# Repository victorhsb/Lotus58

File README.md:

# Lotus 58

Starting with simple tweaks to the Lily58 Glow before ordering a set of PCB's it quickly spiraled out of control, and I ended up with what wasn't quite a Lily58 anymore, and although very similar in layout, it is no longer compatible with plate and case design. 

Because of this, it was renamed Lotus58, referencing another flower much like the lily in the name Lily58.

# Lotus 58 Glow

(photo from reddit by u/bduzik)

- Layout very similar to the original Lily58 family
- Per key RGB and RGB underglow
- Kaihl Hot-swap sockets for MX compatible switches
- Can be used as a standalone Gamepad for either hand
- Optional 0.91" OLED Screens and rotary encoders (one each per side)
- All components through-hole and easily soldered for beginners (SMD option for diodes)
- Designed with a sandwich-style plate/case as part of the design

# Layout variations

- Optional plate layout with OLED screen (Encoder can be placed on upper thumb key position)
- Optional plate layout with rotary encoder (Removes OLED screen for that side)  
- Optional plate layout with no hole for OLED or upper encoder (Encoder can be placed on upper thumb key position)

# Parts needed

| Name of part | Qty. | Optional | Remarks | Aliexpress |
| ------------ | ---- | -------- | ------- | --------------- |
| PCB          | 2    | X        | 1,6mm thick | X           |
| Top plate         | 2 | X        | Optional layouts for OLED or encoder in top position. | X |
| Bottom plate         | 2 | X        | X | X |
| Kailh hotswap socket | 56-58 | X | Qty. depends on layout. | [link](https://www.aliexpress.com/item/-/4001051840976.html?spm=a2g0s.8937460.0.0.6f132e0eKYB5RQ&_ga=2.174414626.1036705865.1612730332-979734211.1611132916&_gac=1.119713146.1611132916.CjwKCAiAxp-ABhALEiwAXm6IyZF-HtTdP3MQioG5GOxLvsaJfBbhqTGIQbmV0LXKDx2MZSDJJJTbaBoCPkoQAvD_BwE) |
| Diodes 1N4841 (TH) or 1N4148W (SMD) | 56-58 | X | Qty. depends on layout. TH recommended for beginners. | [link(TH)](https://www.aliexpress.com/item/HOT-SELL-100-PCS-1N4148-DO-35-IN4148-Silicon-Switching-Diode-FREE-SHIPPMENT/32660088529.html?spm=a2g0s.8937460.0.0.c1b82e0edjrOT3&_ga=2.216963734.1036705865.1612730332-979734211.1611132916&_gac=1.53192282.1611132916.CjwKCAiAxp-ABhALEiwAXm6IyZF-HtTdP3MQioG5GOxLvsaJfBbhqTGIQbmV0LXKDx2MZSDJJJTbaBoCPkoQAvD_BwE) or [link(SMD)](https://www.aliexpress.ru/item/-/1005002059571417.html?spm=a2g0s.8937460.0.0.c1b82e0edjrOT3&_ga=2.216963734.1036705865.1612730332-979734211.1611132916&_gac=1.53192282.1611132916.CjwKCAiAxp-ABhALEiwAXm6IyZF-HtTdP3MQioG5GOxLvsaJfBbhqTGIQbmV0LXKDx2MZSDJJJTbaBoCPkoQAvD_BwE) |
| Capacitors 100 nF | 0-4 | ✔ | Qty. depends on layout. 2 needed for each encoder installed. | [link](https://www.aliexpress.com/item/-/32971478818.html?spm=a2g0s.8937460.0.0.6f132e0eKYB5RQ&_ga=2.149198518.1036705865.1612730332-979734211.1611132916&_gac=1.48473428.1611132916.CjwKCAiAxp-ABhALEiwAXm6IyZF-HtTdP3MQioG5GOxLvsaJfBbhqTGIQbmV0LXKDx2MZSDJJJTbaBoCPkoQAvD_BwE) |
| Resistor 4.7 kOhm | 2 | X | Meant to be mounted only on one side | [link](https://www.aliexpress.com/item/-/32847047012.html?spm=a2g0s.8937460.0.0.c1b82e0edjrOT3&_ga=2.241041155.1036705865.1612730332-979734211.1611132916&_gac=1.219449963.1611132916.CjwKCAiAxp-ABhALEiwAXm6IyZF-HtTdP3MQioG5GOxLvsaJfBbhqTGIQbmV0LXKDx2MZSDJJJTbaBoCPkoQAvD_BwE) |
| 0.91" OLED Display | 0-2 | ✔ | Qty. depends on layout. | [link](https://www.aliexpress.com/item/-/4001028384269.html?spm=a2g0s.8937460.0.0.c1b82e0edjrOT3&_ga=2.241041155.1036705865.1612730332-979734211.1611132916&_gac=1.219449963.1611132916.CjwKCAiAxp-ABhALEiwAXm6IyZF-HtTdP3MQioG5GOxLvsaJfBbhqTGIQbmV0LXKDx2MZSDJJJTbaBoCPkoQAvD_BwE) |
| TRRS jack PJ-320A | 2 | X | X | [link](https://www.aliexpress.com/item/-/4000114275750.html?spm=a2g0s.8937460.0.0.c1b82e0edjrOT3&_ga=2.148895671.1036705865.1612730332-979734211.1611132916&_gac=1.262958974.1611132916.CjwKCAiAxp-ABhALEiwAXm6IyZF-HtTdP3MQioG5GOxLvsaJfBbhqTGIQbmV0LXKDx2MZSDJJJTbaBoCPkoQAvD_BwE) |
| M2 * 10 mm standoff | 10 | X | Rounded, max 3.7 mm in diameter | [link](https://www.aliexpress.com/item/-/32863484622.html?spm=a2g0s.8937460.0.0.c1b82e0edjrOT3&_ga=2.215809815.1036705865.1612730332-979734211.1611132916&_gac=1.26395343.1611132916.CjwKCAiAxp-ABhALEiwAXm6IyZF-HtTdP3MQioG5GOxLvsaJfBbhqTGIQbmV0LXKDx2MZSDJJJTbaBoCPkoQAvD_BwE) |
| M2 * 4 mm screw | 20 | X | 4-8 mm length fits, low profile hex head recommended | [link](https://www.aliexpress.com/item/-/32966917947.html?spm=a2g0s.8937460.0.0.c1b82e0edjrOT3&_ga=2.246923140.1036705865.1612730332-979734211.1611132916&_gac=1.263439230.1611132916.CjwKCAiAxp-ABhALEiwAXm6IyZF-HtTdP3MQioG5GOxLvsaJfBbhqTGIQbmV0LXKDx2MZSDJJJTbaBoCPkoQAvD_BwE) |
| TRRS cable | 1 | X | Needs to be 4 poles, more common 3 poles cable creates a shortcircuit | [link](https://www.aliexpress.com/item/32905903526.html?spm=a2g0o.productlist.0.0.1ea55b40PsHOY6&algo_pvid=74ac6da4-21fa-4152-a7a7-805ba558a2d8&algo_expid=74ac6da4-21fa-4152-a7a7-805ba558a2d8-1&btsid=2100bb4c16148500192992030ee115&ws_ab_test=searchweb0_0,searchweb201602_,searchweb201603_) |
| Silicon pads | 10 | X | X | [link](https://www.aliexpress.com/item/-/32912066603.html?spm=a2g0s.8937460.0.0.6f132e0eKYB5RQ&_ga=2.145547188.1036705865.1612730332-979734211.1611132916&_gac=1.57255896.1611132916.CjwKCAiAxp-ABhALEiwAXm6IyZF-HtTdP3MQioG5GOxLvsaJfBbhqTGIQbmV0LXKDx2MZSDJJJTbaBoCPkoQAvD_BwE) |
| Pro Micro | 2 | X | Can be built with various ProMicro clones as well as Elite C (Or nice!nano for a wireless keyboard) | [link](https://www.aliexpress.com/item/-/32849563958.html?spm=a2g0s.8937460.0.0.c1b82e0edjrOT3&_ga=2.175422242.1036705865.1612730332-979734211.1611132916&_gac=1.225165928.1611132916.CjwKCAiAxp-ABhALEiwAXm6IyZF-HtTdP3MQioG5GOxLvsaJfBbhqTGIQbmV0LXKDx2MZSDJJJTbaBoCPkoQAvD_BwE) |
| Rotary Encoder | 0-2 | ✔ | Qty. depends on layout. | [link](https://www.aliexpress.com/item/10000056483250.html?spm=a2g0o.productlist.0.0.64951c5fKcPiug&algo_pvid=b530d9b1-fbd2-4598-bf53-bece1343826f&algo_expid=b530d9b1-fbd2-4598-bf53-bece1343826f-2&btsid=2100bdd016135510210168102eefcc&ws_ab_test=searchweb0_0,searchweb201602_,searchweb201603_) |
| Rotary Encoder Knob | 0-2 | ✔ | One needed for each encoder. Clearance for max 24 mm diameter, pick halfshaft or spline according to encoder choice.  | [link](https://www.aliexpress.com/item/10000056483250.html?spm=a2g0o.productlist.0.0.64951c5fKcPiug&algo_pvid=b530d9b1-fbd2-4598-bf53-bece1343826f&algo_expid=b530d9b1-fbd2-4598-bf53-bece1343826f-2&btsid=2100bdd016135510210168102eefcc&ws_ab_test=searchweb0_0,searchweb201602_,searchweb201603_) |
| SK6812 mini (3535) | 56-70 | ✔ | Qty. depends on layout. Optional 12 pcs required for underglow. | [link](https://www.aliexpress.com/item/-/4001361956752.html?spm=a2g0s.8937460.0.0.6f132e0eCg84IE&_ga=2.137862832.1036705865.1612730332-979734211.1611132916&_gac=1.14797764.1611132916.CjwKCAiAxp-ABhALEiwAXm6IyZF-HtTdP3MQioG5GOxLvsaJfBbhqTGIQbmV0LXKDx2MZSDJJJTbaBoCPkoQAvD_BwE) |

# Things to note when ordering PCB's

**If you are not aiming at modifying things, don't look for the gerber files in the folders, pretty please! And don't open yet another issue about it! The gerber files are where they belong, zipped up in releases.**

Most PCB manufacturers have a MOQ of 5 PCB's, meaning you end up with 2½ keyboards when finished. To make it possible to build Lotus58 at a reasonable cost, the plate designs use breakaway parts and can easily double as a backplate. For instance, 5 PCB's + 5 OLED plates + 5 Encoder plates give you a couple of options without being wasteful.  

The recommended PCB thickness is 1.6 mm, as the thickness of the SK6812mini RGB LED's are in fact 1.6 mm, making them sit flush 'inside' the PCB and easier to solder. Similarly, for the top plate, a thickness of 1.6 mm is recommended to allow the keyswitches to grip the plate and lock in place securely.

If ordering from [JLPCB](https://www.jlpcb.com) the plate Gerber files include a reference putting the added serial etc on a breakaway part for a clean look with minimal cost, if using another manufacturer it's possible they have additional fee's for removing the extra text, or you should consider plotting the Gerber files yourself with the correct reference for your manufacturer.

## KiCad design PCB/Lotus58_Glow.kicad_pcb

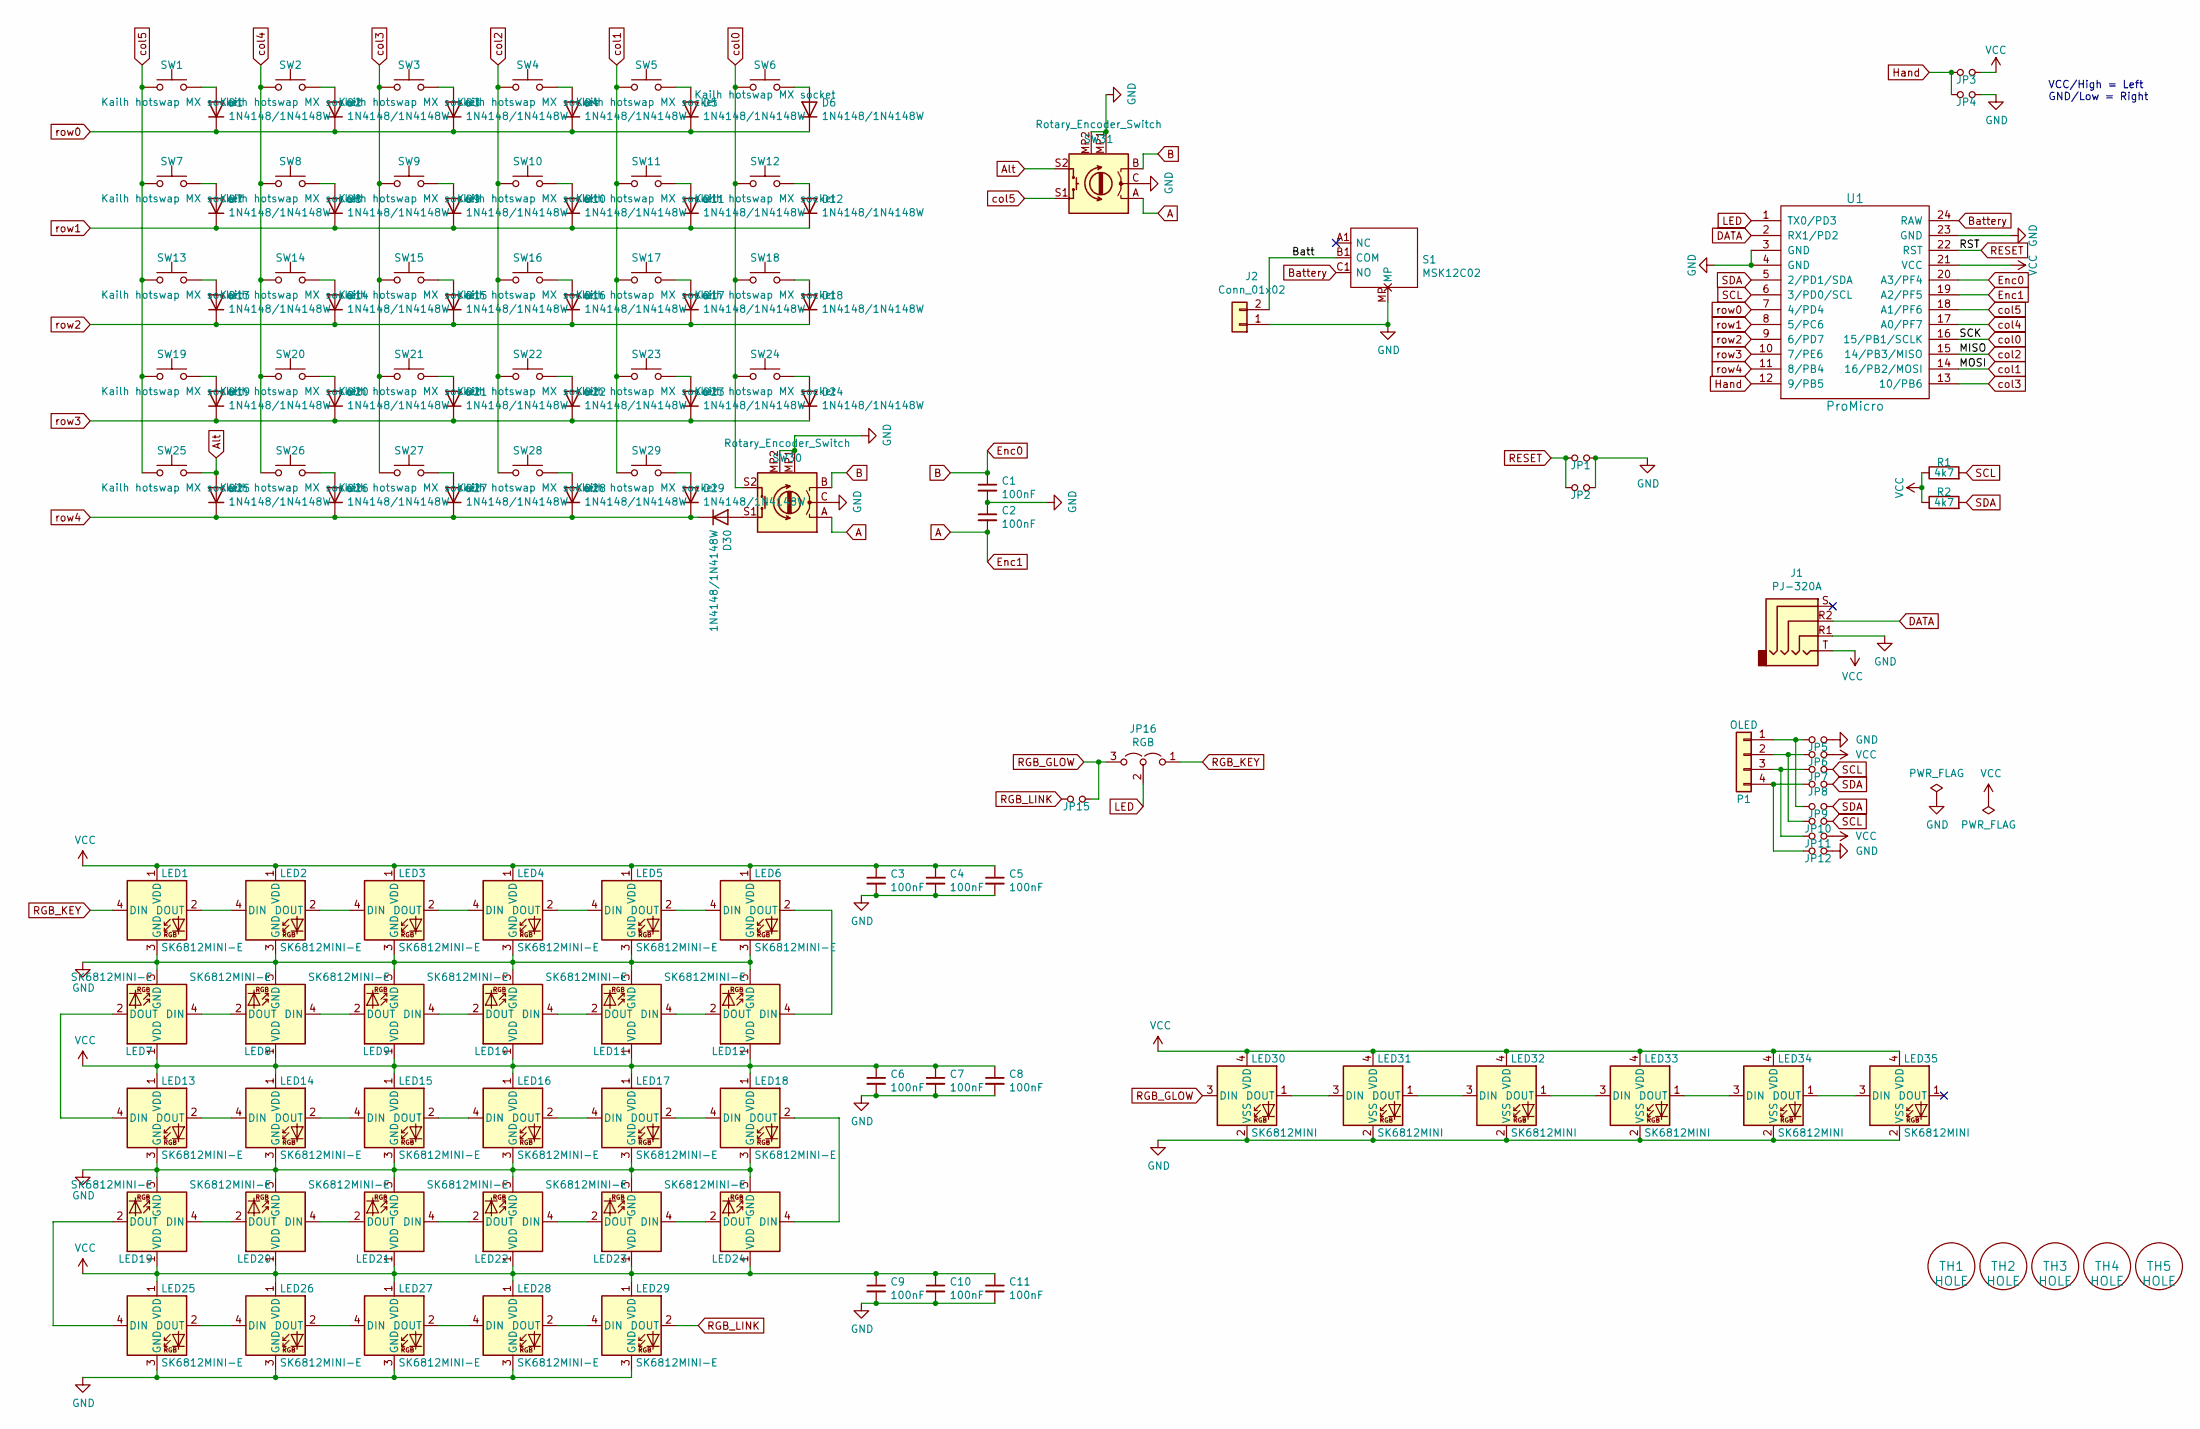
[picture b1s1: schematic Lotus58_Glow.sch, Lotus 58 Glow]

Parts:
C1, C2, C3, C4, C5, C6, C7, C8, C9, C10, C11: 100nF; RESISTOR_Reversible
D1, D2, D3, D4, D5, D6, D7, D8, D9, D10, D11, D12, D13, D14, D15, D16, D17, D18, D19, D20, D21, D22, D23, D24, D25, D26, D27, D28, D29, D30: 1N4148/1N4148W; Diode_DO35_SOD123
J1: PJ-320A; MJ-4PP-9_alim
J2: Conn_01x02; PinHeader_1x02_P2.54mm_Vertical
JP1, JP2: RESET; Jumper_Mini
JP3: LEFT; Jumper_Mini
JP4: RIGHT; Jumper_Mini
JP5, JP6, JP7, JP8, JP9, JP10, JP11, JP12: Jumper_NO_Small; Jumper_Mini
JP15: FULL; Jumper_Mini
JP16: RGB; SolderJumper-3_P1.3mm_Open_Pad1.0x1.5mm
LED1, LED2, LED3, LED4, LED5, LED6, LED7, LED8, LED9, LED10, LED11, LED12, LED13, LED14, LED15, LED16, LED17, LED18, LED19, LED20, LED21, LED22, LED23, LED24, LED25, LED26, LED27, LED28, LED29: SK6812MINI-E; MX_SK6812MINI-E_REVERSIBLE
LED30, LED31, LED32, LED33, LED34, LED35: SK6812MINI; LED_SK6812MINI_PLCC4_3.5x3.5mm_P1.75mm
P1: OLED; SSD1306-0.91-OLED-4pin-128x32
R1, R2: 4k7; R_Axial_DIN0207_L6.3mm_D2.5mm_P7.62mm_Horizontal
S1: MSK12C02; Manufacturer_Part_Number MSK12C02
SW1, SW2, SW3, SW4, SW5, SW6, SW7, SW8, SW9, SW10, SW11, SW12, SW13, SW14, SW15, SW16, SW17, SW18, SW19, SW20, SW21, SW22, SW23, SW24, SW25, SW26, SW27, SW28, SW29: Kailh hotswap MX socket; Kailh_socket_MX_reversible_RGB
SW30: Rotary_Encoder_Switch; RotaryEncoder_Alps_EC11E-Switch_Vertical_H20_special
SW31: Rotary_Encoder_Switch; RotaryEncoder_Alps_EC11E-Switch_Special
TH1, TH2, TH3, TH4, TH5: HOLE; MountingHole_3.7mm
U1: ProMicro; ProMicro_Reversible

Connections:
/Batt: J2.2, S1.B1 (COM)
A: C2.2, SW30.A, SW31.A, U1.19 (A2/PF5)
Alt: D25.2 (A), SW25.2, SW31.S2
B: C1.1, SW30.B, SW31.B, U1.20 (A3/PF4)
Battery: S1.C1 (NO), U1.24 (RAW)
DATA: J1.R2, U1.2 (RX1/PD2)
GND: C1.2, C2.1, C3.2, C4.2, C5.2, C6.2, C7.2, C8.2, C9.2, C10.2, C11.2, J1.R1, J2.1, JP1.2, JP2.2, JP4.2, JP5.2, JP12.2, LED1.3 (GND), LED2.3 (GND), LED3.3 (GND), LED4.3 (GND), LED5.3 (GND), LED6.3 (GND), LED7.3 (GND), LED8.3 (GND), LED9.3 (GND), LED10.3 (GND), LED11.3 (GND), LED12.3 (GND), LED13.3 (GND), LED14.3 (GND), LED15.3 (GND), LED16.3 (GND), LED17.3 (GND), LED18.3 (GND), LED19.3 (GND), LED20.3 (GND), LED21.3 (GND), LED22.3 (GND), LED23.3 (GND), LED24.3 (GND), LED25.3 (GND), LED26.3 (GND), LED27.3 (GND), LED28.3 (GND), LED29.3 (GND), LED30.2 (VSS), LED31.2 (VSS), LED32.2 (VSS), LED33.2 (VSS), LED34.2 (VSS), LED35.2 (VSS), S1.MP, SW30.C, SW30.MP1 (GND), SW30.MP2 (GND), SW31.C, SW31.MP1 (GND), SW31.MP2 (GND), U1.3 (GND), U1.4 (GND), U1.23 (GND)
Hand: JP3.1, JP4.1, U1.12 (9/PB5)
LED: JP16.2 (C), U1.1 (TX0/PD3)
unnamed: D1.2 (A), SW1.2
unnamed: D2.2 (A), SW2.2
unnamed: D3.2 (A), SW3.2
unnamed: D4.2 (A), SW4.2
unnamed: D5.2 (A), SW5.2
unnamed: D6.2 (A), SW6.2
unnamed: D7.2 (A), SW7.2
unnamed: D8.2 (A), SW8.2
unnamed: D9.2 (A), SW9.2
unnamed: D10.2 (A), SW10.2
unnamed: D11.2 (A), SW11.2
unnamed: D12.2 (A), SW12.2
unnamed: D13.2 (A), SW13.2
unnamed: D14.2 (A), SW14.2
unnamed: D15.2 (A), SW15.2
unnamed: D16.2 (A), SW16.2
unnamed: D17.2 (A), SW17.2
unnamed: D18.2 (A), SW18.2
unnamed: D19.2 (A), SW19.2
unnamed: D20.2 (A), SW20.2
unnamed: D21.2 (A), SW21.2
unnamed: D22.2 (A), SW22.2
unnamed: D23.2 (A), SW23.2
unnamed: D24.2 (A), SW24.2
unnamed: D26.2 (A), SW26.2
unnamed: D27.2 (A), SW27.2
unnamed: D28.2 (A), SW28.2
unnamed: D29.2 (A), SW29.2
unnamed: D30.2 (A), SW30.S1
unnamed: JP5.1, JP9.1, P1.1
unnamed: JP6.1, JP10.1, P1.2
unnamed: JP7.1, JP11.1, P1.3
unnamed: JP8.1, JP12.1, P1.4
unnamed: LED1.2 (DOUT), LED2.4 (DIN)
unnamed: LED2.2 (DOUT), LED3.4 (DIN)
unnamed: LED3.2 (DOUT), LED4.4 (DIN)
unnamed: LED4.2 (DOUT), LED5.4 (DIN)
unnamed: LED5.2 (DOUT), LED6.4 (DIN)
unnamed: LED7.4 (DIN), LED8.2 (DOUT)
unnamed: LED8.4 (DIN), LED9.2 (DOUT)
unnamed: LED9.4 (DIN), LED10.2 (DOUT)
unnamed: LED10.4 (DIN), LED11.2 (DOUT)
unnamed: LED11.4 (DIN), LED12.2 (DOUT)
unnamed: LED6.2 (DOUT), LED12.4 (DIN)
unnamed: LED13.2 (DOUT), LED14.4 (DIN)
unnamed: LED7.2 (DOUT), LED13.4 (DIN)
unnamed: LED14.2 (DOUT), LED15.4 (DIN)
unnamed: LED15.2 (DOUT), LED16.4 (DIN)
unnamed: LED16.2 (DOUT), LED17.4 (DIN)
unnamed: LED17.2 (DOUT), LED18.4 (DIN)
unnamed: LED18.2 (DOUT), LED24.4 (DIN)
unnamed: LED19.2 (DOUT), LED25.4 (DIN)
unnamed: LED19.4 (DIN), LED20.2 (DOUT)
unnamed: LED20.4 (DIN), LED21.2 (DOUT)
unnamed: LED21.4 (DIN), LED22.2 (DOUT)
unnamed: LED22.4 (DIN), LED23.2 (DOUT)
unnamed: LED23.4 (DIN), LED24.2 (DOUT)
unnamed: LED25.2 (DOUT), LED26.4 (DIN)
unnamed: LED26.2 (DOUT), LED27.4 (DIN)
unnamed: LED27.2 (DOUT), LED28.4 (DIN)
unnamed: LED28.2 (DOUT), LED29.4 (DIN)
unnamed: LED30.1 (DOUT), LED31.3 (DIN)
unnamed: LED31.1 (DOUT), LED32.3 (DIN)
unnamed: LED32.1 (DOUT), LED33.3 (DIN)
unnamed: LED33.1 (DOUT), LED34.3 (DIN)
unnamed: LED34.1 (DOUT), LED35.3 (DIN)
RESET: JP1.1, JP2.1, U1.22 (RST)
RGB_GLOW: JP15.2, JP16.3 (B), LED30.3 (DIN)
RGB_KEY: JP16.1 (A), LED1.4 (DIN)
RGB_LINK: JP15.1, LED29.2 (DOUT)
SCL: JP7.2, JP10.2, R1.2, U1.6 (3/PD0/SCL)
SDA: JP8.2, JP9.2, R2.2, U1.5 (2/PD1/SDA)
VCC: C3.1, C4.1, C5.1, C6.1, C7.1, C8.1, C9.1, C10.1, C11.1, J1.T, JP3.2, JP6.2, JP11.2, LED1.1 (VDD), LED2.1 (VDD), LED3.1 (VDD), LED4.1 (VDD), LED5.1 (VDD), LED6.1 (VDD), LED7.1 (VDD), LED8.1 (VDD), LED9.1 (VDD), LED10.1 (VDD), LED11.1 (VDD), LED12.1 (VDD), LED13.1 (VDD), LED14.1 (VDD), LED15.1 (VDD), LED16.1 (VDD), LED17.1 (VDD), LED18.1 (VDD), LED19.1 (VDD), LED20.1 (VDD), LED21.1 (VDD), LED22.1 (VDD), LED23.1 (VDD), LED24.1 (VDD), LED25.1 (VDD), LED26.1 (VDD), LED27.1 (VDD), LED28.1 (VDD), LED29.1 (VDD), LED30.4 (VDD), LED31.4 (VDD), LED32.4 (VDD), LED33.4 (VDD), LED34.4 (VDD), LED35.4 (VDD), R1.1, R2.1, U1.21 (VCC)
col0: SW6.1, SW12.1, SW18.1, SW24.1, SW30.S2, U1.16 (15/PB1/SCLK)
col1: SW5.1, SW11.1, SW17.1, SW23.1, SW29.1, U1.14 (16/PB2/MOSI)
col2: SW4.1, SW10.1, SW16.1, SW22.1, SW28.1, U1.15 (14/PB3/MISO)
col3: SW3.1, SW9.1, SW15.1, SW21.1, SW27.1, U1.13 (10/PB6)
col4: SW2.1, SW8.1, SW14.1, SW20.1, SW26.1, U1.17 (A0/PF7)
col5: SW1.1, SW7.1, SW13.1, SW19.1, SW25.1, SW31.S1, U1.18 (A1/PF6)
row0: D1.1 (K), D2.1 (K), D3.1 (K), D4.1 (K), D5.1 (K), D6.1 (K), U1.7 (4/PD4)
row1: D7.1 (K), D8.1 (K), D9.1 (K), D10.1 (K), D11.1 (K), D12.1 (K), U1.8 (5/PC6)
row2: D13.1 (K), D14.1 (K), D15.1 (K), D16.1 (K), D17.1 (K), D18.1 (K), U1.9 (6/PD7)
row3: D19.1 (K), D20.1 (K), D21.1 (K), D22.1 (K), D23.1 (K), D24.1 (K), U1.10 (7/PE6)
row4: D25.1 (K), D26.1 (K), D27.1 (K), D28.1 (K), D29.1 (K), D30.1 (K), U1.11 (8/PB4)

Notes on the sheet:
VCC/High = Left GND/Low = Right

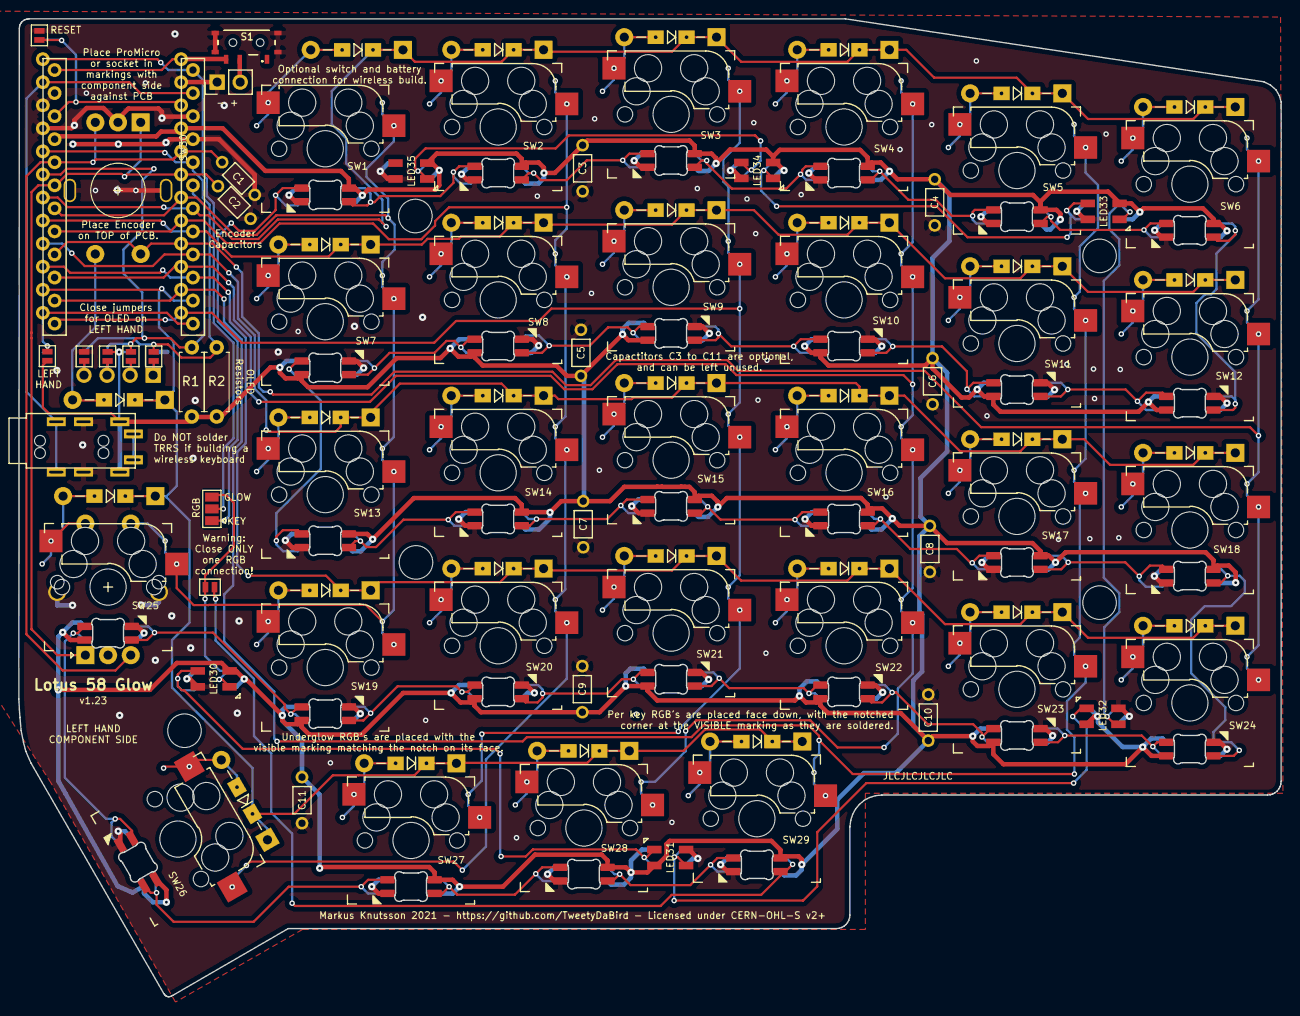
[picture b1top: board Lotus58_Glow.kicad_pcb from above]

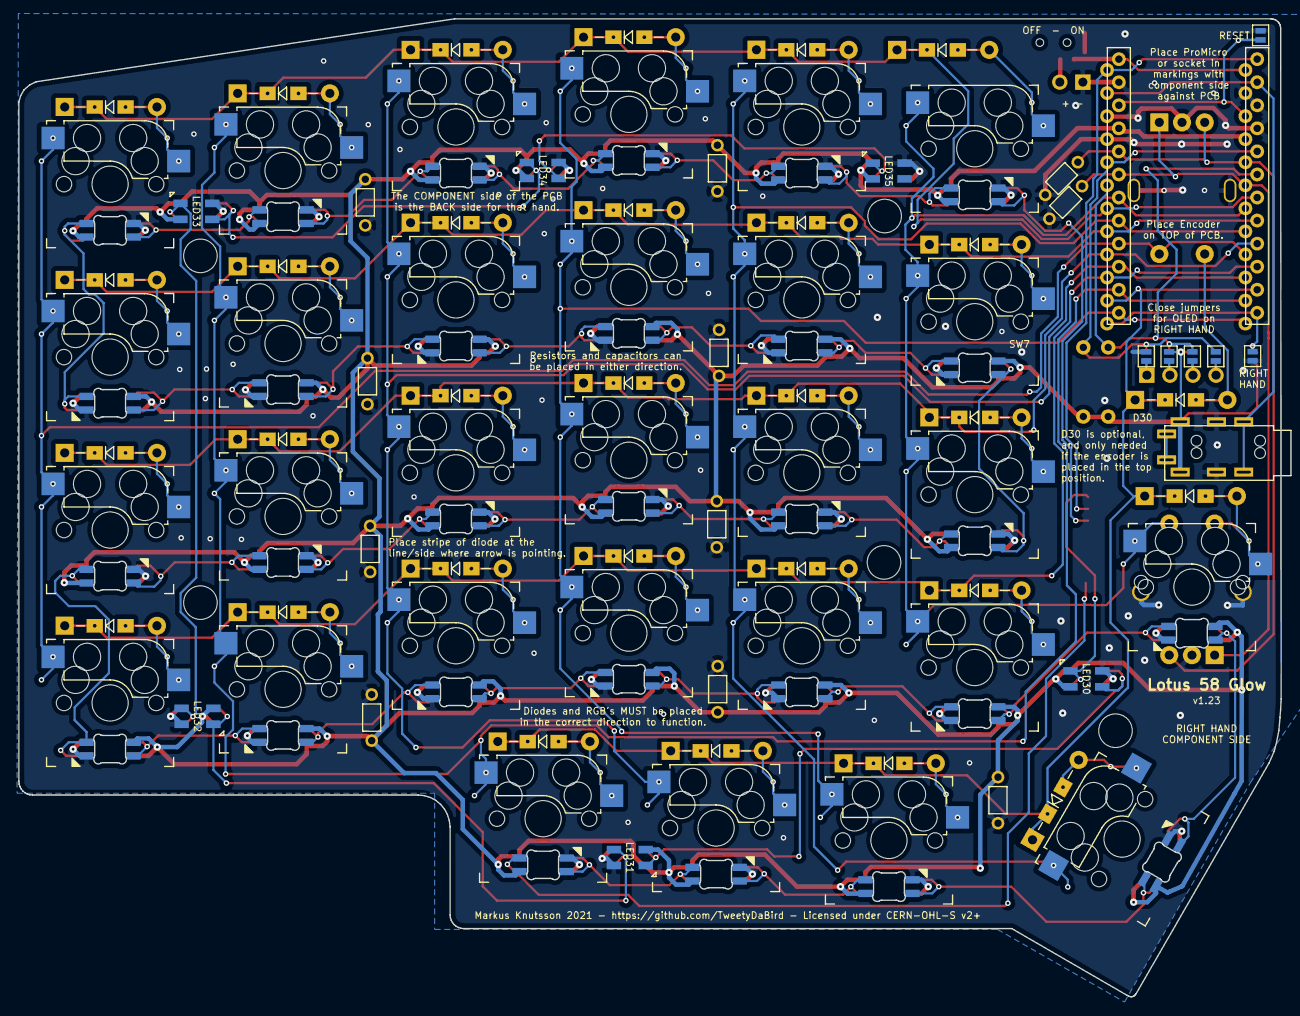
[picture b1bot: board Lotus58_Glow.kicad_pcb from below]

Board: 2 copper layers, 139.1 x 107.7 mm, 133 parts (38 on the bottom side), 93 nets.

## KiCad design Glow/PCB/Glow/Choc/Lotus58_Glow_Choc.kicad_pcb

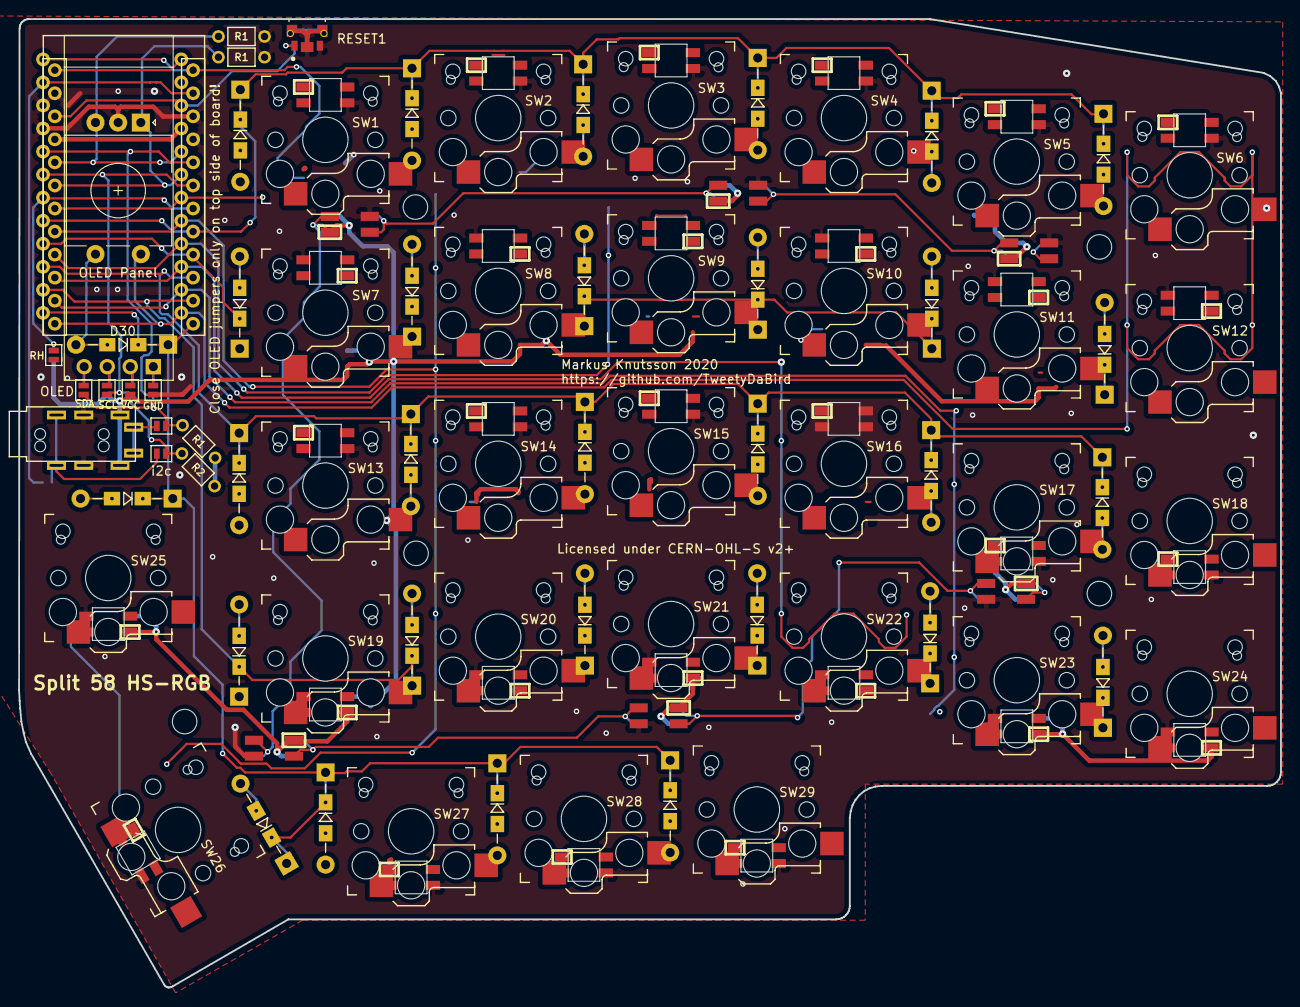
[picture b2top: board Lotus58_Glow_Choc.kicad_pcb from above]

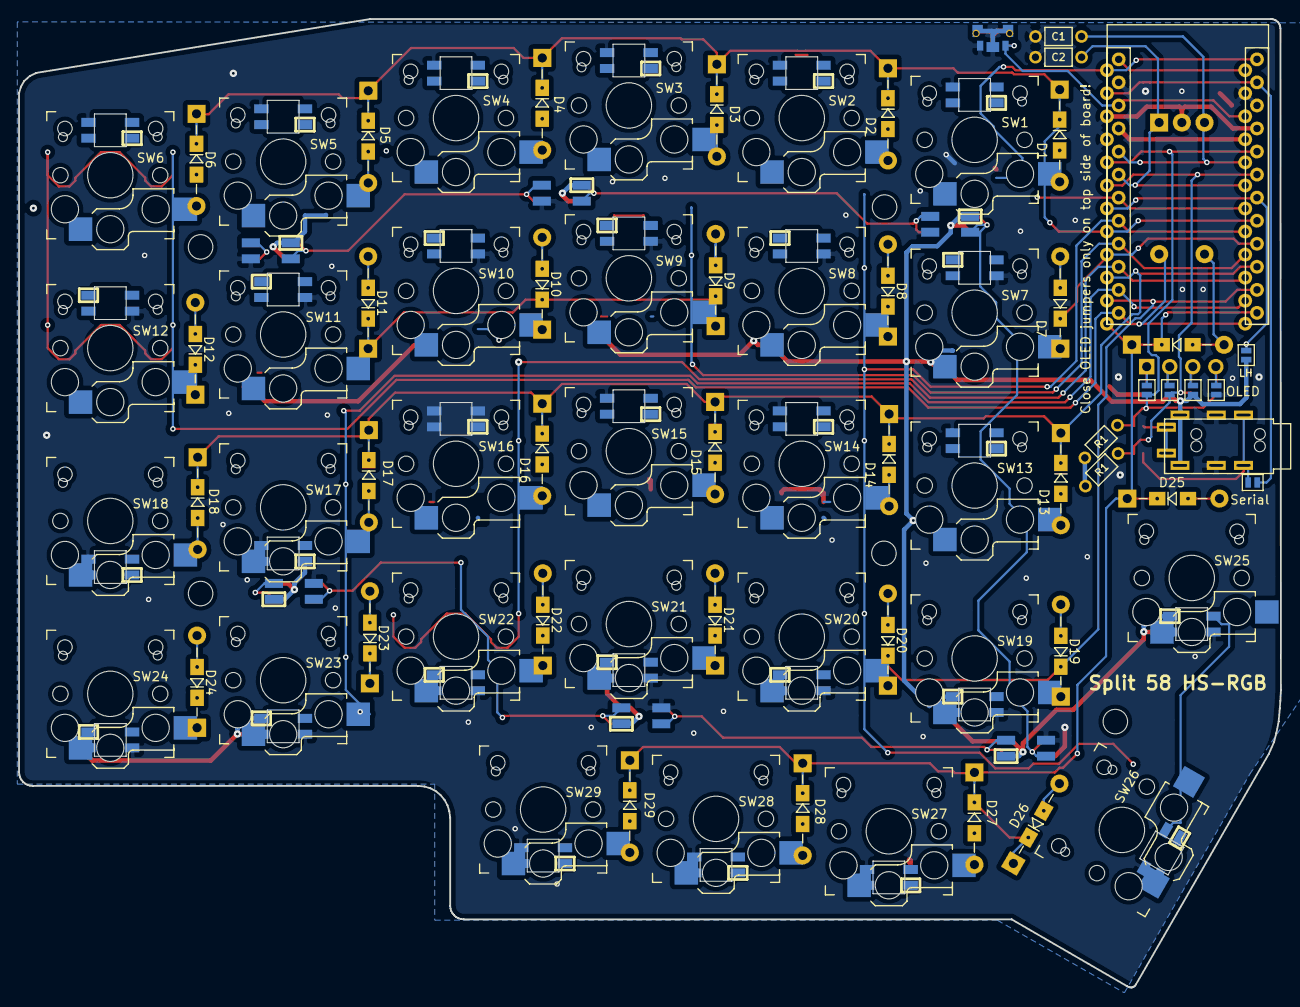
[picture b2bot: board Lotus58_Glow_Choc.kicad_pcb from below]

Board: 2 copper layers, 139.1 x 106.7 mm, 121 parts (37 on the bottom side), 91 nets.

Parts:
C1, C2: C_Small; RESISTOR_Reversible
D1, D2, D3, D4, D5, D6, D7, D8, D9, D10, D11, D12, D13, D14, D15, D16, D17, D18, D19, D20, D21, D22, D23, D24, D25, D26, D27, D28, D29, D30: D; Diode_DO35_SOD123
J1: AudioJack4; MJ-4PP-9_alim
JP1, JP2, JP3, JP4, JP5, JP6, JP7, JP8, JP9, JP10, JP11: Jumper_NO_Small; Jumper_Mini
JP12: LH; Jumper_Mini
JP13: RH; Jumper_Mini
L1, L2, L3, L4, L5, L6, L7, L8, L9, L10, L11, L12, L13, L14, L15, L16, L17, L18, L19, L20, L21, L22, L23, L24, L25, L26, L27, L28, L29: SK6812mini; SK6812MINI_Midmount_Reversible
L30, L31, L32, L33, L34, L35: SK6812mini; SK6812MINI_Reversible
P4: OLED; SSD1306-0.91-OLED-4pin-128x32
R1, R2: R; RESISTOR_Reversible
RESET1: EVP-AKE31A; Panasonic-EVP-AKE31A-MFG_reversible
SW1, SW2, SW3, SW4, SW5, SW6, SW7, SW8, SW9, SW10, SW11, SW12, SW13, SW14, SW15, SW16, SW17, SW18, SW19, SW20, SW21, SW22, SW23, SW24, SW25, SW26, SW27, SW28, SW29: SW_PUSH; Kailh_socket_PG1350_PG1353_reversible
SW30: Rotary_Encoder_Switch; RotaryEncoder_EC11-no-legs
TH3, TH4, TH5, TH6, TH7: HOLE; MountingHole_2.7mm_M2.5
U1: ProMicro; ProMicro_Reversible

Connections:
DATA: JP11.2, U1.2
Enc0: C1.1, SW30.B, U1.20
Enc1: C2.2, SW30.A, U1.19
GND: C1.2, C2.1, J1.R1, JP1.2, JP8.2, JP13.2, L1.2, L2.2, L3.2, L4.2, L5.2, L6.2, L7.2, L8.2, L9.2, L10.2, L11.2, L12.2, L13.2, L14.2, L15.2, L16.2, L17.2, L18.2, L19.2, L20.2, L21.2, L22.2, L23.2, L24.2, L25.2, L26.2, L27.2, L28.2, L29.2, L30.2, L31.2, L32.2, L33.2, L34.2, L35.2, RESET1.1, RESET1.2, RESET1.3, RESET1.A, SW30.C, U1.3, U1.4, U1.23
Hand: JP12.1, JP13.1, U1.7
LED: L1.3, U1.1
unnamed: D1.2, SW1.2
unnamed: D2.2, SW2.2
unnamed: D3.2, SW3.2
unnamed: D4.2, SW4.2
unnamed: D5.2, SW5.2
unnamed: D6.2, SW6.2
unnamed: D7.2, SW7.2
unnamed: D8.2, SW8.2
unnamed: D9.2, SW9.2
unnamed: D10.2, SW10.2
unnamed: D11.2, SW11.2
unnamed: D12.2, SW12.2
unnamed: D13.2, SW13.2
unnamed: D14.2, SW14.2
unnamed: D15.2, SW15.2
unnamed: D16.2, SW16.2
unnamed: D17.2, SW17.2
unnamed: D18.2, SW18.2
unnamed: D19.2, SW19.2
unnamed: D20.2, SW20.2
unnamed: D21.2, SW21.2
unnamed: D22.2, SW22.2
unnamed: D23.2, SW23.2
unnamed: D24.2, SW24.2
unnamed: D25.2, SW25.2
unnamed: D26.2, SW26.2
unnamed: D27.2, SW27.2
unnamed: D28.2, SW28.2
unnamed: D29.2, SW29.2
unnamed: D30.2, SW30.S1
unnamed: J1.R2, JP9.2, JP11.1
unnamed: J1.S, JP10.1
unnamed: JP1.1, JP5.1, P4.1
unnamed: JP2.1, JP6.1, P4.2
unnamed: JP3.1, JP7.1, P4.3
unnamed: JP4.1, JP8.1, P4.4
unnamed: L1.1, L2.3
unnamed: L2.1, L3.3
unnamed: L3.1, L4.3
unnamed: L4.1, L5.3
unnamed: L5.1, L6.3
unnamed: L7.3, L8.1
unnamed: L8.3, L9.1
unnamed: L9.3, L10.1
unnamed: L10.3, L11.1
unnamed: L11.3, L12.1
unnamed: L6.1, L12.3
unnamed: L13.1, L14.3
unnamed: L7.1, L13.3
unnamed: L14.1, L15.3
unnamed: L15.1, L16.3
unnamed: L16.1, L17.3
unnamed: L17.1, L18.3
unnamed: L18.1, L24.3
unnamed: L19.1, L25.3
unnamed: L19.3, L20.1
unnamed: L20.3, L21.1
unnamed: L21.3, L22.1
unnamed: L22.3, L23.1
unnamed: L23.3, L24.1
unnamed: L25.1, L26.3
unnamed: L26.1, L27.3
unnamed: L27.1, L28.3
unnamed: L28.1, L29.3
unnamed: L29.1, L30.3
unnamed: L30.1, L31.3
unnamed: L31.1, L32.3
unnamed: L32.1, L35.3
unnamed: L33.3, L34.1
unnamed: L34.3, L35.1
RESET: RESET1.A', U1.22
SCL: JP3.2, JP6.2, JP9.1, R2.2, U1.6
SDA: JP4.2, JP5.2, JP10.2, R1.2, U1.5
VCC: J1.T, JP2.2, JP7.2, JP12.2, L1.4, L2.4, L3.4, L4.4, L5.4, L6.4, L7.4, L8.4, L9.4, L10.4, L11.4, L12.4, L13.4, L14.4, L15.4, L16.4, L17.4, L18.4, L19.4, L20.4, L21.4, L22.4, L23.4, L24.4, L25.4, L26.4, L27.4, L28.4, L29.4, L30.4, L31.4, L32.4, L33.4, L34.4, L35.4, R1.1, R2.1, U1.21
col0: SW6.1, SW12.1, SW18.1, SW24.1, SW30.S2, U1.13
col1: SW5.1, SW11.1, SW17.1, SW23.1, SW29.1, U1.14
col2: SW4.1, SW10.1, SW16.1, SW22.1, SW28.1, U1.15
col3: SW3.1, SW9.1, SW15.1, SW21.1, SW27.1, U1.16
col4: SW2.1, SW8.1, SW14.1, SW20.1, SW26.1, U1.17
col5: SW1.1, SW7.1, SW13.1, SW19.1, SW25.1, U1.18
row0: D1.1, D2.1, D3.1, D4.1, D5.1, D6.1, U1.8
row1: D7.1, D8.1, D9.1, D10.1, D11.1, D12.1, U1.9
row2: D13.1, D14.1, D15.1, D16.1, D17.1, D18.1, U1.10
row3: D19.1, D20.1, D21.1, D22.1, D23.1, D24.1, U1.11
row4: D25.1, D26.1, D27.1, D28.1, D29.1, D30.1, U1.12

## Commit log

2019-07-19 Create version with in-switch SK6812mini LEDs
2019-07-19 Tighten up some traces
2019-07-19 Remove old gerber files
2019-07-20 Update SK6812mini footprint
2019-07-20 Add underglow
2019-07-20 Clean up routing new thumb key
2019-07-28 Add ground planes
2019-09-03 Add some branding
2019-09-03 Add gitignore
2019-09-03 Commit files not ignored by gitignore
2019-09-03 Move files to root directory
2019-09-04 Update LICENSE
2020-12-10 New design
2020-12-11 Start of Choc
2020-12-11 moving files
2020-12-11 Added Plate files
2020-12-11 added gerbers MX version
2020-12-12 Rename and Cleanup
2020-12-12 Added optional encoder layout
2020-12-12 Updated silkscreen
    New name!
2020-12-15 Revised footprint
2020-12-15 Added Image
2020-12-15 Updated Plates
2021-01-04 Adjusted plate
2021-01-27 Rearranging folders
2021-01-27 Created Wireless
2021-02-08 RGB midmount footprints
    Fixed mirror image pinout
2021-02-12 Component values/BOM added
2021-02-12 BOM file updated
2021-02-12 Changed Readme.md
2021-02-13 Readme.md
2021-02-13 Some words were changed to human words
2021-02-13 changed 2 to 0
2021-02-14 Update README.md
    Clarified a few options.
2021-02-15 Added OLED to plate design
2021-02-15 Update README.md
    Not that there cannot be 4 encoders installed.
2021-02-15 Gerbers an zip moved to releases
2021-02-16 Blank front plate option added
2021-02-16 Changed reame.md
2021-02-25 Corrected mounting holes
2021-03-04 Corrected underglow vs per key RGB
2021-03-04 Update README.md
    Added explanation on RGB LED's.
2021-03-04 Update README.md
    Corrected spelling
2021-03-04 Updated plates to remove break-away parts
2021-03-09 Improve grammar
2021-03-15 Minor changes to silkscreen
    - Added missing lables for jumpers
    - Removed labels for holes(?)
    - Corrected marker for RGB LED's
2021-05-14 Update README.md
    Corrected bad link
2021-05-17 Update README.md
    Removed MiniE from parts list due to incompatible pinout.
2021-05-17 Update README.md
    Added information about reset switch.
2021-05-21 add dxf files for laser cut plates
2021-05-29 Add dxf for top plate with encoder cutout
2021-06-01 Added Bottom Plate
    With M3 holes for tent/tilt
2021-06-01 Renamed/moved files
    Laser cut plates in a separate folder
2021-08-12 Fixed JLCPCB Spelling mistake
2021-08-12 Fixed Spelling mistake "Lotsu" to "Lotus"
2021-08-13 nothing
2021-08-13 Fixed Wrong No TENT bottom plate
2021-08-30 Fixed typo
2021-10-07 Updated PCB
2021-10-14 Updated PCB
    Split RGB for under-glow and per-key.
    Added capacitors on RGB.
    Edited encoder footprint for ESD grounding.
    OLED display repositioned.
    Simplified i2c/serial.
    Simplified reset.
2021-10-19 General Housekeeping
2021-10-19 More Housekeeping
2021-10-19 Initial v1.21
2021-12-02 updated v1.22
2021-12-11 v1.22 final touches
2021-12-17 replaced DXF files
2021-12-17 v1.23
2021-12-17 removed /test
2022-02-11 restore plate DXF files
    The original files were corrupted in
    https://github.com/TweetyDaBird/Lotus58/commit/1c34fa41cd076e58e1640e762ec52977901df85a
    and this commit brings the original files forward without modification.
    Closes https://github.com/TweetyDaBird/Lotus58/issues/31
2022-03-12 added my custom lotus58 keymap with brazilian keybindings (abnt2)
2022-03-12 added a readme explaining how to compile my custom keymap

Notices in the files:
Glow/PCB/Glow/Choc/Lotus58_Glow_Choc.kicad_pcb:
Licensed under CERN-OHL-S v2 or any superseding version
PCB/Lotus58_Glow.kicad_pcb:
Markus Knutsson 2021 - https://github.com/TweetyDaBird - Licensed under CERN-OHL-S v2+
